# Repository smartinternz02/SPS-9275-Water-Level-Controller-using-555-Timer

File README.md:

# SPS-9275-Water-Level-Controller-using-555-Timer

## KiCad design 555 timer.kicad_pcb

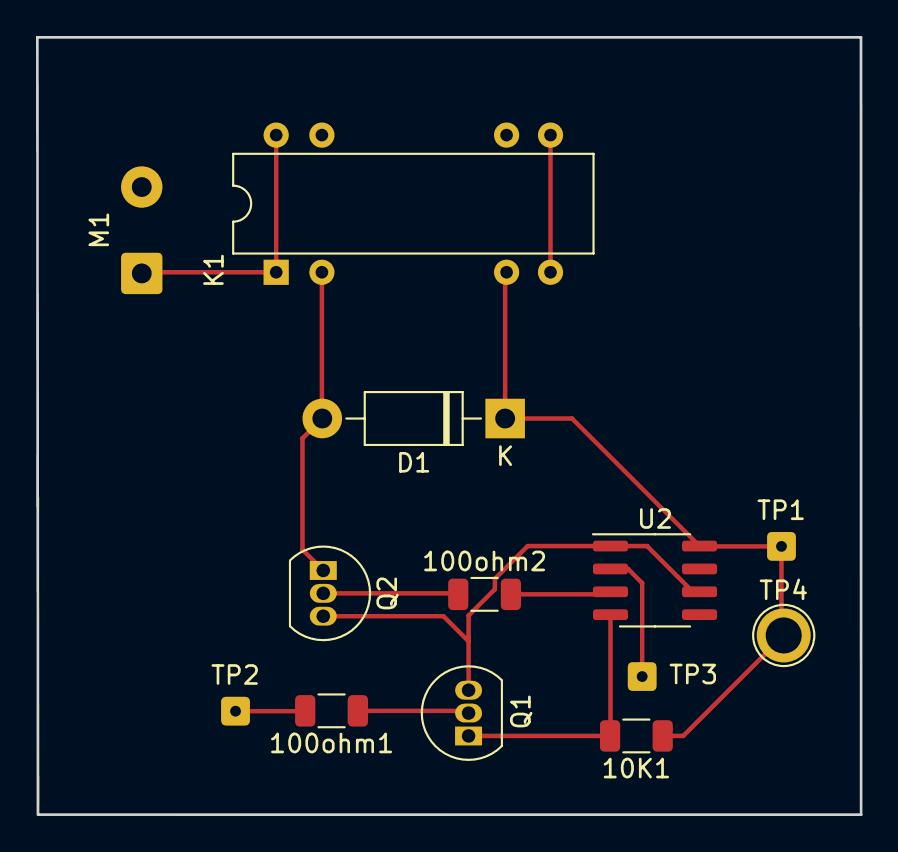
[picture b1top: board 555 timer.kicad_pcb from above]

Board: 2 copper layers, 45.8 x 43.2 mm, 13 parts (0 on the bottom side), 11 nets.

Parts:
10K1, 100ohm1, 100ohm2: R; R_1206_3216Metric
D1: 1N4007; D_DO-41_SOD81_P10.16mm_Horizontal
K1: DIPxx-1Axx-11x; Relay_StandexMeder_DIP_LowProfile
M1: Motor_DC; SolderWire-0.5sqmm_1x02_P4.8mm_D0.9mm_OD2.3mm
Q1, Q2: BC548; TO-92_Inline
TP1: VCC; SolderWire-0.1sqmm_1x01_D0.4mm_OD1mm
TP2: UP; SolderWire-0.1sqmm_1x01_D0.4mm_OD1mm
TP3: LOW; SolderWire-0.1sqmm_1x01_D0.4mm_OD1mm
TP4: +9V VCC; TestPoint_Plated_Hole_D2.0mm
U2: LM555; SOIC-8_3.9x4.9mm_P1.27mm

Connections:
GNDREF: Q1.3, Q2.3, U2.1, U2.6
unnamed: 10K1.1, D1.1, K1.6, TP1.1, TP4.1, U2.8
unnamed: 10K1.2, Q1.1, U2.4
unnamed: 100ohm1.1, Q1.2
unnamed: 100ohm1.2, TP2.1
unnamed: 100ohm2.1, Q2.2
unnamed: 100ohm2.2, U2.3
unnamed: D1.2, K1.2, Q2.1
unnamed: K1.1, K1.14, M1.1
unnamed: K1.7, K1.8
unnamed: TP3.1, U2.2
